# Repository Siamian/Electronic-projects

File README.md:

# Uk-ady-elektroniczne
Układy elektroniczne

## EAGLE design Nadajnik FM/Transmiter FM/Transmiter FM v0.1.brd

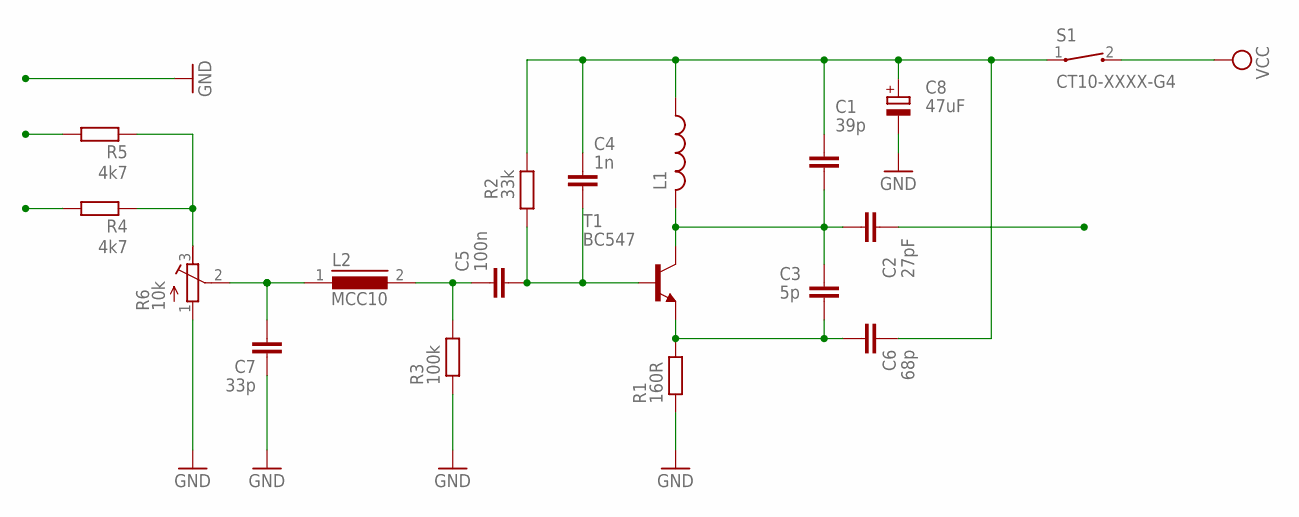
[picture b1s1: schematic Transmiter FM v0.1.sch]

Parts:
C1: 39p; C025-024X044
C2: 27pF; C025-024X044
C3: 5p; C025-024X044
C4: 1n; C025-024X044
C5: 100n; C025-024X044
C6: 68p; C025-024X044
C7: 33p; C025-024X044
C8: 47uF; E5-10,5
L1: L-US0204/5; 0204/5
L2: MCC10
R1: 160R; 0204V
R2: 33k; 0204V
R3: 100k; 0204V
R4, R5: 4k7; 0204V
R6: 10k; RTRIM4G/J
S1: CT10-XXXX-G4
T1: BC547; TO92

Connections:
GND: C7.1, C8.-, R1.1, R3.1, R6.1 (A)
unnamed: C1.2, C2.2, C3.1, L1.2, T1.3 (C)
unnamed: C7.2, L2.1, R6.2 (S)
unnamed: C5.1, L2.2, R3.2
unnamed: C4.2, C5.2, R2.1, T1.2 (B)
unnamed: C1.1, C4.1, C6.1, C8.+, L1.1, R2.2, S1.1
unnamed: R4.1, R5.1, R6.3 (E)
unnamed: C3.2, C6.2, R1.2, T1.1 (E)
VCC: S1.2

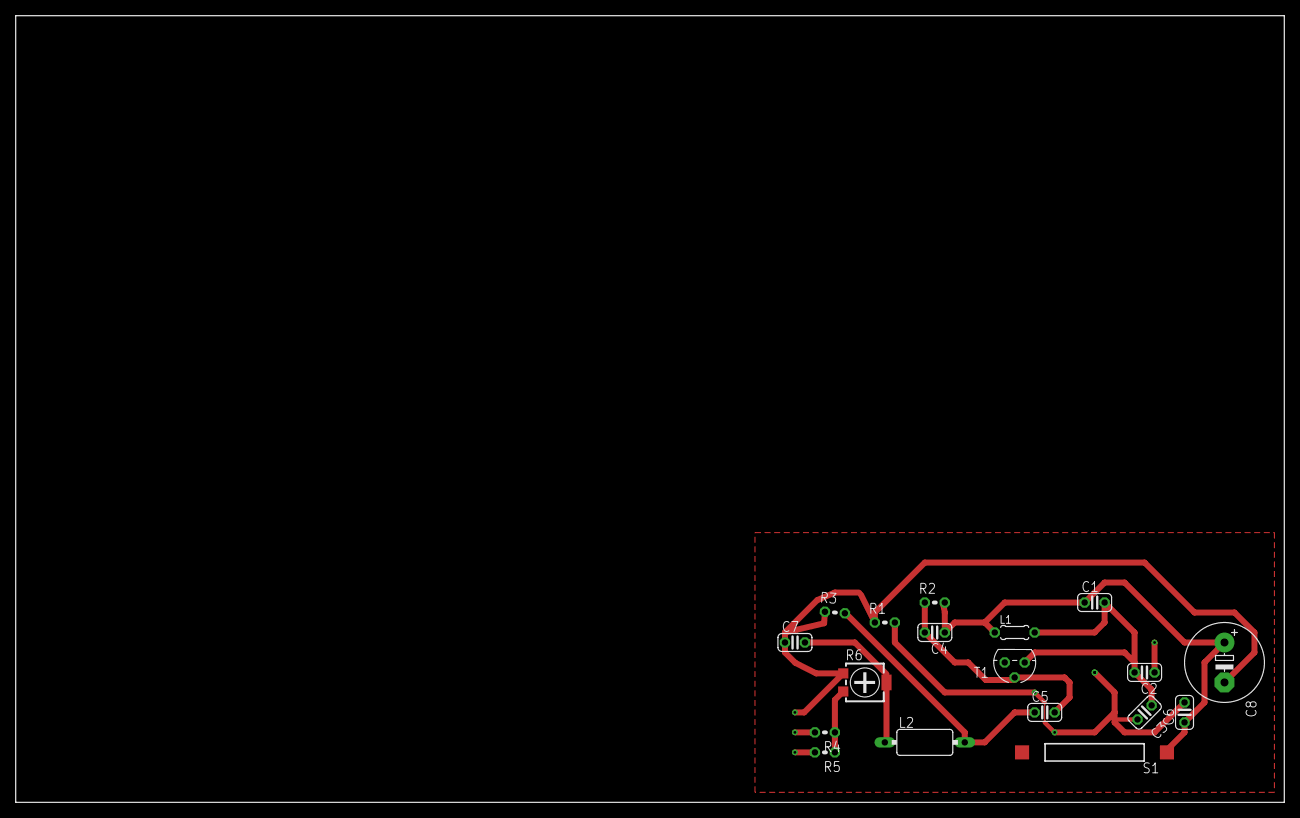
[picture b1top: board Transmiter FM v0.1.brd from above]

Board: 2 copper layers, 161.3 x 100.0 mm, 18 parts (0 on the bottom side), 8 nets.
